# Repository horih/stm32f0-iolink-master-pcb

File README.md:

# C104 IOLink-master-PCB
## 回路図PDF
[PDFファイル](iolink_pcb.pdf)
## パーツリスト
| 番号 | パーツ名 | 値 | その他 |
| :--- | :---: | :---: | :---: |
| C1,C6,C8,C11,C13,C18 | 0603 ceramic capacitor | 4.7uF| Vmax=3.3v|
| C19,C20,C21 | 0603 ceramic capacitor | 4.7uF | Vmax=30v |
| C2,C23 | 6.3x5.9 electrolytic capacitor | 47uF | Vmax=30v |
| C3 | 0603 ceramic capacitor | 22uF |　Vmax=3.3v |
| C4 | 0603 ceramic capacitor | 10uF | Vmax=5v | 
| C7,C9,C10,C12,C14,C17 | 0603 ceramic capacitor| 0.1uF |Vmax=5v |
| C15,C16 |0603 ceramic capacitor | 32pF |Vmax=3.3v|
| R1,R2 |0603 registor|60ohm|||
| R3,R4 |0603 registor|10kohm|||
| R5,R7,R11,R12 |0603 registor|10ohm|||
| R6,R8,R9,R10 | 0603 registor|0.2ohm|||
| R13,R17 | 0603 registor|4.7kohm|||
| R15,R16 | 0603 registor|0ohm|||
| D1, D2| 0603 LED|||
| IC1 | LTC2874IFE ||https://mou.sr/3X1CPJl|
| IC2 | AZ1117CH3.3TRG1||https://akizukidenshi.com/catalog/g/g116155/|
| IC3 | M78AR05-0.5||https://akizukidenshi.com/catalog/g/g107179/|
| Q1,Q2 | NDS9936 ||https://akizukidenshi.com/catalog/g/g116757/|
| U1 | STM32F091CCT6||https://mou.sr/4cnDoBN|
| U2 |MCP2562-H-SN||https://mou.sr/4dl9AXA|
| Y1 | Crystal| 8Mhz |https://akizukidenshi.com/catalog/g/g108667/|
| SW1| Push_Switch 6mm H4.3mm||https://akizukidenshi.com/catalog/g/g115969/|
|J1,J2,J4,J5,J6,J7,J8|2.54mm　terminal block||https://akizukidenshi.com/catalog/g/g114217/|

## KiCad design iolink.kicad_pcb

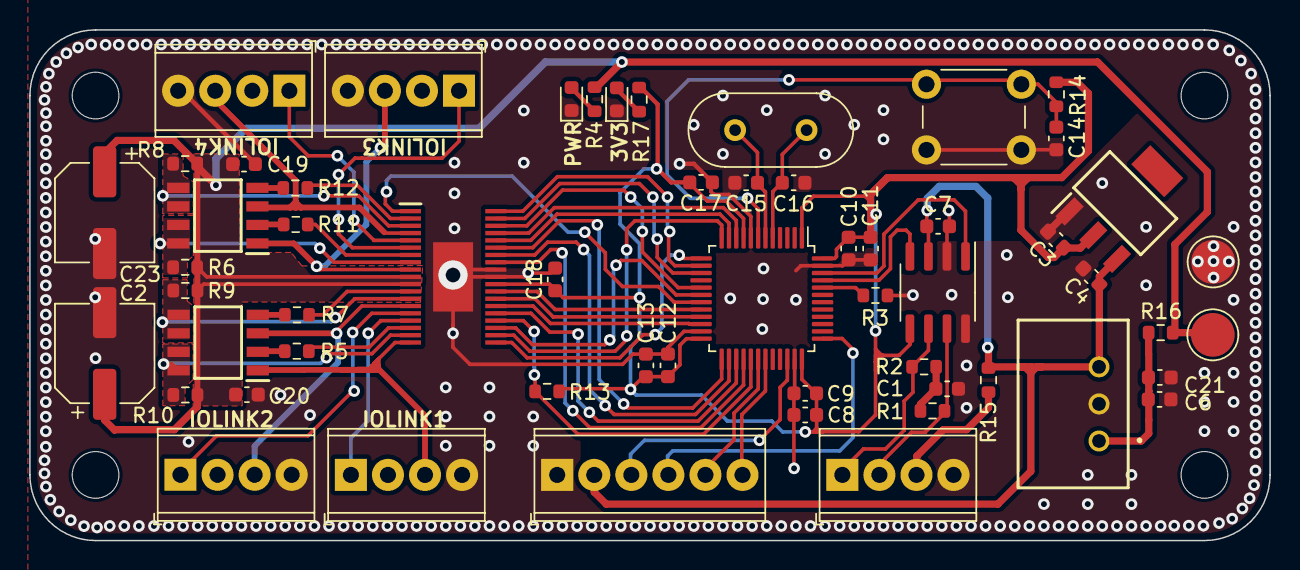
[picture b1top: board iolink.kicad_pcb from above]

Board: 2 copper layers, 85.0 x 35.0 mm, 57 parts (0 on the bottom side), 58 nets.

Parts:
C1, C6, C8, C11, C13, C18, C19, C20, C21: 4.7uF; C_0603_1608Metric
C2, C23: C_Polarized; CP_Elec_6.3x5.9
C3: 22uF; C_0603_1608Metric
C4: 10uF; C_0603_1608Metric
C7, C9, C10, C12, C14, C17: 0.1uF; C_0603_1608Metric
C15, C16: 32pF; C_0603_1608Metric
D1, D2: LED; LED_0603_1608Metric
IC1: LTC2874IFE#PBF; SOP50P640X120-39N
IC2: AZ1117CH-5.0TRG1; SOT230P700X180-4N
IC3: M78AR05-0.5; M78AR05
J1, J4, J5, J6, J7: Screw_Terminal_01x04; TerminalBlock_Phoenix_MPT-0,5-4-2.54_1x04_P2.54mm_Horizontal
J3, J9: Conn_01x01; TestPoint_Pad_D3.0mm
J8: Screw_Terminal_01x06; TerminalBlock_Phoenix_MPT-0,5-6-2.54_1x06_P2.54mm_Horizontal
Q1, Q2: NDS9936; SOIC127P600X175-8N
R1, R2: 60ohm; R_0603_1608Metric
R3, R14: 10kohm; R_0603_1608Metric
R4: 10k; R_0603_1608Metric
R5, R7, R11, R12: 10ohm; R_0603_1608Metric
R6, R8, R9, R10: 0.2ohm; R_0603_1608Metric
R13: 4.7kohm; R_0603_1608Metric
R15, R16: 0; R_0603_1608Metric
R17: 4.7k; R_0603_1608Metric
SW1: SW_Push; SW_PUSH_6mm_H4.3mm
U1: STM32F091CCTx; LQFP-48_7x7mm_P0.5mm
U2: MCP2562-H-SN; SOIC-8_3.9x4.9mm_P1.27mm
Y1: 8Mhz; Crystal_HC18-U_Vertical

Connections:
+3V3: C3.1, C8.1, C9.1, C10.1, C11.1, C12.1, C13.1, C17.1, C18.1, IC1.28 (VL), IC2.2 (OUTPUT), R13.1, R14.2, R17.1, U1.1 (VBAT), U1.9 (VDDA), U1.24 (VDD), U1.36 (VDDIO2), U1.48 (VDD), U2.5 (Vio)
+5V: C4.1, C7.1, IC2.3 (INPUT), IC3.3 (+VOUT), J8.2, R15.1, U2.3 (VDD)
+24V: C2.1, C19.1, C20.1, C23.1, IC1.10 (SENSE+), IC1.11 (VDD), J3.1, R4.1, R6.2, R8.2, R9.2, R10.2, R16.2
/CAN_H: J1.2, R1.1, U2.7 (CANH)
/CAN_L: J1.1, R2.2, U2.6 (CANL)
/CAN_RX: U1.45 (PB8), U2.4 (RXD)
/CAN_TX: U1.46 (PB9), U2.1 (TXD)
/IRQ: IC1.23 (~IRQ), R13.2, U1.29 (PA8)
/NRST: C14.2, R14.1, SW1.2, U1.7 (NRST)
/OSC_IN: C16.1, U1.5 (PF0), Y1.2
/OSC_OUT: C15.1, U1.6 (PF1), Y1.1
/SPI2_MISO: IC1.24 (SDO), U1.27 (PB14)
/SPI2_MOSI: IC1.31 (SDI), U1.28 (PB15)
/SPI2_NSS: IC1.33 (~CS), U1.25 (PB12)
/SPI2_SCK: IC1.32 (SCK), U1.26 (PB13)
/SWCLK: J8.4, U1.37 (PA14)
/SWDIO: J8.3, U1.34 (PA13)
/USART1_RX: J8.6, U1.31 (PA10)
/USART1_TX: J8.5, U1.30 (PA9)
/USART2_EN: IC1.22 (TXEN1), U1.18 (PB0)
/USART2_RX: IC1.20 (RXD1), U1.13 (PA3)
/USART2_TX: IC1.21 (TXD1), U1.12 (PA2)
/USART3_EN: IC1.27 (TXEN2), U1.20 (PB2)
/USART3_RX: IC1.25 (RXD2), U1.22 (PB11)
/USART3_TX: IC1.26 (TXD2), U1.21 (PB10)
/USART4_EN: IC1.36 (TXEN3), U1.17 (PA7)
/USART4_RX: IC1.34 (RXD3), U1.11 (PA1)
/USART4_TX: IC1.35 (TXD3), U1.10 (PA0)
/USART6_EN: IC1.1 (TXEN4), U1.19 (PB1)
/USART6_RX: IC1.37 (RXD4), U1.15 (PA5)
/USART6_TX: IC1.38 (TXD4), U1.14 (PA4)
GND: C1.1, C2.2, C3.2, C4.2, C6.2, C7.2, C8.2, C9.2, C10.2, C11.2, C12.2, C13.2, C14.1, C15.2, C16.2, C17.2, C18.2, C19.2, C20.2, C21.2, C23.2, D1.1 (K), D2.1 (K), IC1.29 (GND_1), IC1.30 (GND_2), IC1.39 (GND_3), IC2.1 (ADJ/GND), IC3.2 (GND), J1.4, J4.4, J5.4, J6.4, J7.4, J8.1, J9.1, R3.2, SW1.1, U1.8 (VSSA), U1.23 (VSS), U1.35 (VSS), U1.47 (VSS), U2.2 (VSS), U2.8 (STBY)
unnamed: C1.2, R1.2, R2.1
unnamed: D1.2 (A), R4.2
unnamed: D2.2 (A), R17.2
unnamed: IC1.16 (CQ1), J5.1
unnamed: IC1.15 (CQ2), J4.1
unnamed: IC1.6 (CQ3), J6.1
unnamed: IC1.5 (CQ4), J7.1
unnamed: IC1.17 (GATE1), R5.2
unnamed: IC1.12 (GATE2), R7.2
unnamed: IC1.7 (GATE3), R11.2
unnamed: IC1.2 (GATE4), R12.2
unnamed: IC1.19 (L+1), J5.3, Q1.1 (S1)
unnamed: IC1.14 (L+2), J4.3, Q1.3 (S2)
unnamed: IC1.9 (L+3), J6.3, Q2.1 (S1)
unnamed: IC1.4 (L+4), J7.3, Q2.3 (S2)
unnamed: IC1.18 (SENSE-1), Q1.7 (D1_1), Q1.8 (D1_2), R10.1
unnamed: IC1.13 (SENSE-2), Q1.5 (D2_1), Q1.6 (D2_2), R9.1
unnamed: IC1.8 (SENSE-3), Q2.7 (D1_1), Q2.8 (D1_2), R6.1
unnamed: IC1.3 (SENSE-4), Q2.5 (D2_1), Q2.6 (D2_2), R8.1
unnamed: J1.3, R15.2
unnamed: Q1.2 (G1), R5.1
unnamed: Q1.4 (G2), R7.1
unnamed: Q2.2 (G1), R11.1
unnamed: Q2.4 (G2), R12.1
unnamed: R3.1, U1.44 (PF11)
VBUS: C6.1, C21.1, IC3.1 (+VIN), R16.1

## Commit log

2024-08-11 init
2024-08-11 Create LICENSE
